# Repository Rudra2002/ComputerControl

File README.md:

# 🖥️ ComputerControl

> **Remotely power on, restart, and monitor your PC from anywhere in the world** — using an ESP32 microcontroller, MQTT, and a sleek web dashboard.

---

## 📋 Table of Contents

- [Overview](#overview)
- [Architecture](#architecture)
- [Features](#features)
- [Schematic](#schematic)
- [Pin Mapping](#pin-mapping)
- [Hardware Requirements](#hardware-requirements)
- [Software Prerequisites](#software-prerequisites)
- [Getting Started](#getting-started)
  - [1. Flash the ESP32 Firmware](#1-flash-the-esp32-firmware)
  - [2. Configure WiFi & MQTT](#2-configure-wifi--mqtt)
  - [3. Deploy the Web Dashboard](#3-deploy-the-web-dashboard)
- [MQTT Topic Reference](#mqtt-topic-reference)
- [Security Features](#security-features)
- [Project Structure](#project-structure)
- [Legacy System](#legacy-system)
- [Contributing](#contributing)
- [License](#license)

---

## Overview

**ComputerControl** is an IoT project that lets you control your PC's power and restart buttons remotely over the internet. An ESP32 physically connects to your PC's front-panel headers via relay modules and monitors the power LED to detect the PC's on/off state.

The system communicates over **MQTT** (with WebSocket support), enabling a static web dashboard — deployable on **Cloudflare Pages** or any CDN — to send commands and receive real-time status updates from anywhere.

---

## Architecture

```
┌──────────────────────────────────────────────────────────────────┐
│                        CLOUD / INTERNET                          │
│                                                                  │
│  ┌─────────────────────┐         ┌────────────────────────────┐  │
│  │   Web Dashboard     │◄──WSS──►│     MQTT Broker            │  │
│  │  (Cloudflare Pages) │         │  (broker.emqx.io or self)  │  │
│  │                     │         │                            │  │
│  │  • Power ON/OFF     │         │  Topics:                   │  │
│  │  • Restart          │         │  computercontrol/{id}/...  │  │
│  │  • Live status      │         │    /status                 │  │
│  │  • Activity log     │         │    /command                │  │
│  └─────────────────────┘         │    /response               │  │
│                                  │    /lwt                    │  │
│                                  └────────────┬───────────────┘  │
│                                               │                  │
└───────────────────────────────────────────────┼──────────────────┘
                                                │ MQTT (TCP 1883)
                                                │
┌───────────────────────────────────────────────┼──────────────────┐
│  LOCAL NETWORK                                │                  │
│                                               │                  │
│                        ┌──────────────────────▼───────────────┐  │
│                        │         ESP32 WROOM-32               │  │
│                        │                                      │  │
│                        │  GPIO 25 ──► Power Relay ──► PWR_SW  │  │
│                        │  GPIO 26 ──► Restart Relay ► RST_SW  │  │
│                        │  GPIO 34 ◄── PC Power LED (input)    │  │
│                        │  GPIO  2 ──► Onboard LED (status)    │  │
│                        │                                      │  │
│                        │  WiFiManager captive portal          │  │
│                        │  Config reset via BOOT button        │  │
│                        └──────────────────────────────────────┘  │
│                                       │                          │
│                              ┌────────▼────────┐                 │
│                              │    Your PC      │                 │
│                              │  (ATX headers)  │                 │
│                              └─────────────────┘                 │
└──────────────────────────────────────────────────────────────────┘
```

---

## Features

### Firmware (ESP32)
- **Relay control** — Momentary press simulation for power and restart buttons
- **PC status monitoring** — Reads the motherboard power LED to detect ON/OFF state
- **WiFiManager** — No hardcoded WiFi credentials; configure via captive portal
- **MQTT with LWT** — Last Will & Testament for instant offline detection
- **Rate limiting** — Prevents accidental rapid-fire relay triggers (3s cooldown)
- **Persistent config** — MQTT settings saved to flash via the `Preferences` library
- **Config reset** — Hold the BOOT button on power-up to factory reset

### Web Dashboard
- **Modern glassmorphism UI** — Dark theme with ambient background effects
- **Real-time status ring** — Visual indicator for PC online/offline/unknown states
- **MQTT over WebSocket** — Connects via `wss://` for TLS-encrypted communication
- **Activity log** — Timestamped log of all events and commands
- **Toast notifications** — Non-intrusive feedback for actions and errors
- **Settings persistence** — Browser `localStorage` with base64 encoding
- **Auto-disconnect** — Automatically disconnects after 30 minutes of inactivity
- **Responsive design** — Works on desktop, tablet, and mobile

---

## Schematic

The circuit schematic is designed in **KiCad** and included in the [`kicad-circuit/`](kicad-circuit/) directory.

> Full schematic available as [PDF](kicad-circuit/scematic.pdf) and [SVG](kicad-circuit/pc-power-remote-switch.svg). The KiCad project files (`.kicad_sch`, `.kicad_pcb`, `.kicad_pro`) are also included for editing.

### Key Circuit Details

| Component | Connection | Purpose |
|---|---|---|
| **Relay Module 1** | ESP32 GPIO 25 → Relay IN | Simulates PC power button press |
| **Relay Module 2** | ESP32 GPIO 26 → Relay IN | Simulates PC restart button press |
| **Voltage Divider / Optocoupler** | PC Power LED → ESP32 GPIO 34 | Safely reads the PC power LED state |
| **ESP32 Onboard LED** | GPIO 2 | Visual feedback (MQTT connected, boot, etc.) |

### Wiring to ATX Front Panel Headers

The relay outputs connect **in parallel** to the motherboard's front-panel power switch (`PWR_SW`) and reset switch (`RST_SW`) headers. When the ESP32 activates a relay for 500ms, it mimics a physical button press.

```
Motherboard PWR_SW Header:       Motherboard RST_SW Header:
  ┌───┐                            ┌───┐
  │ + ├──── Relay 1 COM            │ + ├──── Relay 2 COM
  │ - ├──── Relay 1 NO             │ - ├──── Relay 2 NO
  └───┘                            └───┘
```

> **⚠️ Note:** GPIO 34 is an *input-only* pin on the ESP32 — perfect for reading the PC power LED but cannot output signals.

---

## Pin Mapping

| GPIO | Direction | Function | Notes |
|-----:|-----------|----------|-------|
| `34` | Input | PC Power LED sensor | Input-only GPIO, no internal pull-up |
| `25` | Output | Power relay trigger | Active HIGH for 500ms |
| `26` | Output | Restart relay trigger | Active HIGH for 500ms |
| `2`  | Output | Onboard LED | Indicates MQTT connection & boot |
| `0`  | Input | Config reset button | Hold LOW on boot to reset WiFi/MQTT settings |

---

## Hardware Requirements

| Component | Quantity | Notes |
|---|:---:|---|
| ESP32 WROOM-32 DevKit | 1 | Any ESP32 dev board with GPIO access |
| 5V Relay Module (1-channel) | 2 | One for power, one for restart |
| Jumper Wires (F-F, M-F) | ~10 | For connecting ESP32, relays, and ATX headers |
| USB Cable (Micro-USB / Type-C) | 1 | For flashing and powering the ESP32 |
| PC with ATX Motherboard | 1 | Target PC to control |
| Optocoupler / Voltage divider | 1 | *(Optional)* For safe PC LED reading via GPIO 34 |

---

## Software Prerequisites

| Tool | Purpose | Install |
|------|---------|---------|
| [PlatformIO](https://platformio.org/install/cli) | Firmware build & flash | VS Code extension or CLI |
| [Node.js](https://nodejs.org/) (v18+) | Web dashboard development | Download from nodejs.org |
| [Git](https://git-scm.com/) | Version control | Download from git-scm.com |

---

## Getting Started

### 1. Flash the ESP32 Firmware

```bash
# Clone the repository
git clone https://github.com/Rudra2002/ComputerControl.git
cd ComputerControl

# Build and upload the firmware
cd firmware
pio run --target upload

# Monitor serial output (optional)
pio device monitor --baud 115200
```

> The firmware automatically installs its dependencies (`PubSubClient`, `ArduinoJson`, `WiFiManager`) via PlatformIO.

### 2. Configure WiFi & MQTT

On first boot (or after a config reset), the ESP32 creates a WiFi access point:

| Setting | Value |
|---|---|
| **SSID** | `ComputerControl-Setup` |
| **Password** | `setup1234` |
| **Portal timeout** | 180 seconds |

1. Connect to the `ComputerControl-Setup` WiFi network from your phone or laptop
2. A captive portal opens automatically — enter your **WiFi credentials**
3. Scroll down to **MQTT Configuration** and fill in:
   - **MQTT Broker Host** — e.g. `broker.emqx.io` (free public broker)
   - **MQTT Broker Port** — `1883` (TCP) or `8084` (WebSocket TLS on EMQX)
   - **Device ID** — A unique name like `my-pc-ctrl` (used to build MQTT topics)
   - **MQTT Username / Password** — optional, depends on your broker
4. Click **Save** — the ESP32 connects to WiFi and the MQTT broker

> **To reset configuration:** Hold the **BOOT** button (GPIO 0) while powering on the ESP32. The LED will blink rapidly, and the captive portal will reappear.

### 3. Deploy the Web Dashboard

#### Local Development

```bash
cd web
npm install
npm run dev
# Opens at http://localhost:3000
```

#### Production Build (for Cloudflare Pages, Netlify, etc.)

```bash
cd web
npm run build
# Output in web/dist/ — deploy this folder
```

#### Connecting the Dashboard

1. Open the web dashboard in your browser
2. Enter your MQTT broker's **WebSocket URL** — e.g. `wss://broker.emqx.io:8084/mqtt`
3. Enter the **Device ID** you configured on the ESP32
4. *(Optional)* Enter MQTT username/password if your broker requires authentication
5. Click **Connect** — the dashboard will show real-time PC status

---

## MQTT Topic Reference

All topics follow the pattern: `computercontrol/{device_id}/...`

| Topic | Direction | QoS | Payload | Description |
|---|---|:---:|---|---|
| `…/status` | ESP32 → Web | 0 | `{"pc":1,"uptime":3600,"rssi":-55,"ip":"192.168.1.100"}` | Periodic status (every 2s) |
| `…/command` | Web → ESP32 | 1 | `{"action":"power"}` | Send command (`power`, `restart`, `status`) |
| `…/response` | ESP32 → Web | 0 | `{"success":true,"message":"Power button pressed"}` | Command acknowledgement |
| `…/lwt` | Broker → Web | 1 | `{"online":false}` | Last Will — sent when ESP32 disconnects |

---

## Security Features

| Feature | Layer | Description |
|---|---|---|
| WiFiManager Portal | Firmware | No hardcoded WiFi credentials |
| MQTT Authentication | Firmware + Web | Optional username/password for broker access |
| Command Rate Limiting | Firmware | Min 3-second interval between relay commands |
| Topic Namespacing | MQTT | Unique device ID isolates traffic |
| LWT (Last Will) | MQTT | Broker notifies dashboard if ESP32 drops offline |
| WSS (TLS) | Web | Web dashboard connects via encrypted WebSocket |
| Inactivity Auto-Disconnect | Web | Dashboard disconnects after 30 min of inactivity |
| Settings Obfuscation | Web | localStorage settings encoded with base64 |

---

## Project Structure

```
ComputerControl/
├── firmware/                  # ESP32 firmware (PlatformIO)
│   ├── platformio.ini         # Build config & dependencies
│   └── src/
│       ├── config.h           # Pin definitions, timing, MQTT defaults
│       └── main.cpp           # Main firmware — WiFi, MQTT, relay logic
│
├── web/                       # Web dashboard (Vite + vanilla JS)
│   ├── index.html             # Dashboard HTML (connect screen + dashboard)
│   ├── package.json           # npm dependencies (mqtt.js)
│   ├── vite.config.js         # Vite dev server config
│   └── src/
│       ├── main.js            # MQTT client, UI logic, command handling
│       └── style.css          # Glassmorphism dark theme, animations
│
├── kicad-circuit/             # Hardware schematic (KiCad 8)
│   ├── pc-power-remote-switch.kicad_sch   # Schematic source
│   ├── pc-power-remote-switch.kicad_pcb   # PCB layout
│   ├── pc-power-remote-switch.kicad_pro   # KiCad project file
│   ├── scematic.png           # Schematic render (PNG)
│   ├── scematic.pdf           # Schematic render (PDF)
│   └── pc-power-remote-switch.svg         # Schematic render (SVG)
│
├── LeagacySystem/             # Legacy ESP8266 firmware (archived)
│   ├── esp8266_dashboard/     # Original ESP8266 web server dashboard
│   ├── main_firmware_alpha/   # Alpha firmware
│   ├── check_output_pin/      # GPIO test sketch
│   └── file_upload_littlefs_webserver/    # LittleFS file server
│
├── .gitignore
└── README.md                  # ← You are here
```

---

## Legacy System

The `LeagacySystem/` directory contains the original ESP8266-based implementation that served a web dashboard directly from the microcontroller via LittleFS. This has been superseded by the current ESP32 + MQTT architecture, which offers:

- ✅ **Remote access** — Control from anywhere, not just on local network
- ✅ **Separation of concerns** — Web frontend hosted independently on a CDN
- ✅ **Better security** — MQTT authentication, TLS, rate limiting
- ✅ **Reliability** — LWT for offline detection, auto-reconnect

The legacy code is kept for reference purposes.

---

## Contributing

1. **Fork** the repository
2. **Create** a feature branch (`git checkout -b feature/my-feature`)
3. **Commit** your changes (`git commit -m 'Add my feature'`)
4. **Push** to the branch (`git push origin feature/my-feature`)
5. Open a **Pull Request**

---

## License

This project is open source and available under the [MIT License](LICENSE).

---

<p align="center">
  Built with ❤️ using ESP32 + MQTT + Vite<br/>
  <sub>Designed & developed by <a href="https://github.com/Rudra2002">Rudra</a></sub>
</p>

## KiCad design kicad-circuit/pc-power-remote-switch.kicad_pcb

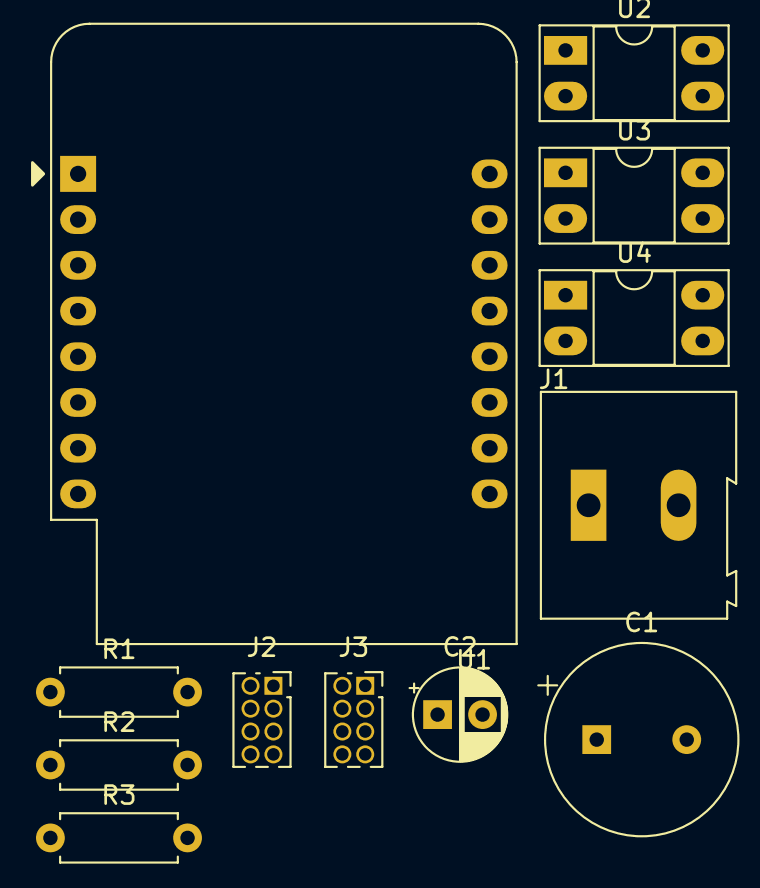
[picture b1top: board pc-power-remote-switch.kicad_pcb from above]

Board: 2 copper layers, 12 parts (0 on the bottom side), 16 nets, no tracks yet.

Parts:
C1: 1000 uF; CP_Radial_Tantal_D10.5mm_P5.00mm
C2: 100nF; CP_Radial_D5.0mm_P2.50mm
J1: TerminalBlock_Altech_AK300-2_P5.00mm
J2: INPUT; PinSocket_2x04_P1.27mm_Vertical
J3: OUTPUT; PinSocket_2x04_P1.27mm_Vertical
R1: 4.7k; R_Axial_DIN0207_L6.3mm_D2.5mm_P7.62mm_Horizontal
R2, R3: 100 ohm; R_Axial_DIN0207_L6.3mm_D2.5mm_P7.62mm_Horizontal
U1: WEMOS_D1_mini; WEMOS_D1_mini_light
U2: Optocoupler Power; DIP-4_W7.62mm_Socket_LongPads
U3: Optocoupler Power Button; DIP-4_W7.62mm_Socket_LongPads
U4: Optocoupler Restart Button; DIP-4_W7.62mm_Socket_LongPads

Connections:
+5V: C1.1, C2.1, J1.2, U1.9 (5V)
GND: C1.2, C2.2, J1.1, R1.2, U1.10 (GND), U3.2, U4.2
unnamed: R2.1, U3.1
unnamed: R3.1, U4.1
unnamed: U1.8 (3V3), U2.4
led+: J2.6, J3.6
led-: J2.2, J3.2
pc_power_mc_input: R1.1, U1.14 (SCL/D1), U2.3
power+: J2.5, J3.5, U2.1
power-: J2.1, J3.1, U2.2
power_button_1: J2.7, J3.7, U3.4
power_button_2: J2.3, J3.3, U3.3
power_button_mc_input: R2.2, U1.13 (SDA/D2)
restart_button_1: J2.8, J3.8, U4.4
restart_button_2: J2.4, J3.4, U4.3
restart_button_mc_input: R3.2, U1.12 (D3)

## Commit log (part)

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2026-03-20 Readme
2026-03-23 added hardware image

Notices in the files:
README.md:
License: MIT
